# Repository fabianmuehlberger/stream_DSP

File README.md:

## Welcome to GitHub Pages

You can use the [editor on GitHub](https://github.com/fabianmuehlberger/stream_DSP/edit/page/README.md) to maintain and preview the content for your website in Markdown files.

Whenever you commit to this repository, GitHub Pages will run [Jekyll](https://jekyllrb.com/) to rebuild the pages in your site, from the content in your Markdown files.

### Markdown

Markdown is a lightweight and easy-to-use syntax for styling your writing. It includes conventions for

```markdown
Syntax highlighted code block

# Header 1
## Header 2
### Header 3

- Bulleted
- List

1. Numbered
2. List

**Bold** and _Italic_ and `Code` text

[Link](url) and 
```

For more details see [Basic writing and formatting syntax](https://docs.github.com/en/github/writing-on-github/getting-started-with-writing-and-formatting-on-github/basic-writing-and-formatting-syntax).

### Jekyll Themes

Your Pages site will use the layout and styles from the Jekyll theme you have selected in your [repository settings](https://github.com/fabianmuehlberger/stream_DSP/settings/pages). The name of this theme is saved in the Jekyll `_config.yml` configuration file.

### Support or Contact

Having trouble with Pages? Check out our [documentation](https://docs.github.com/categories/github-pages-basics/) or [contact support](https://support.github.com/contact) and we’ll help you sort it out.

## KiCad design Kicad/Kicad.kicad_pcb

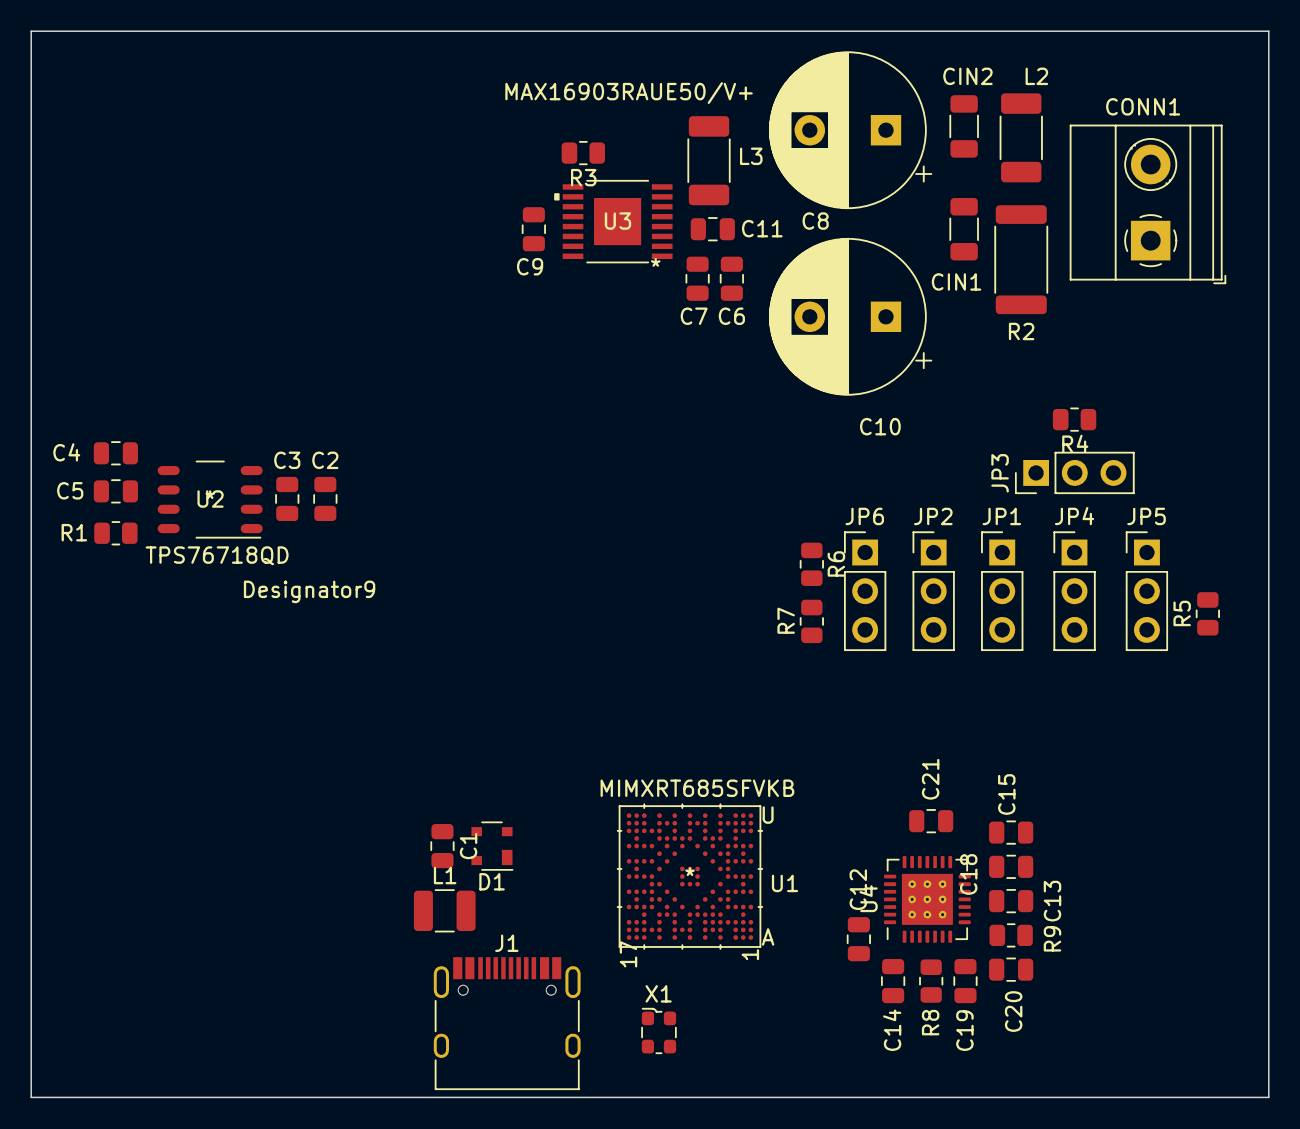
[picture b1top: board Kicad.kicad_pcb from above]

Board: 4 copper layers, 81.2 x 70.0 mm, 47 parts (0 on the bottom side), 38 nets, no tracks yet.

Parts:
C1: 2u2; C_0805_2012Metric
C2, C3, C9, C11, C12, C13, C14, C18, C21: 1u; C_0805_2012Metric
C4, C5: 10uF; C_0805_2012Metric
C6, C7, C15: 4u7; C_0805_2012Metric
C8, C10: 100uF; CP_Radial_D10.0mm_P5.00mm
C19, C20: 2n2; C_0805_2012Metric
CIN1, CIN2: 0.022uF; C_1206_3216Metric
CONN1: Screw_Terminal_01x02; TerminalBlock_Phoenix_MKDS-1,5-2_1x02_P5.00mm_Horizontal
D1: PRTR5V0U2X; SOT-143
J1: USB_C_Receptacle_USB2.0; USB_C_Receptacle_HRO_TYPE-C-31-M-12
JP1, JP2, JP3, JP4, JP5, JP6: Jumper_3_Open; PinHeader_1x03_P2.54mm_Vertical
L1: 330; L_1210_3225Metric
L2: 47; L_2010_5025Metric
L3: 4u7; L_2010_5025Metric
R1: 10k; R_0805_2012Metric
R2: 0.1R; R_2512_6332Metric
R3: 20k; R_0805_2012Metric
R4, R5, R6, R7: 47k; R_0805_2012Metric
R8, R9: 300; R_0805_2012Metric
U1: MIMXRT685SFVKB
U2: TPS76718QD
U3: MAX16903RAUE50/V+; MAX16903RAUE50&slash_V&plus_
U4: ES9033; QFN-28-1EP_5x5mm_P0.5mm_EP3.35x3.35mm_ThermalVias
X1: ECS-2520MV-xxx-xx; Oscillator_SMD_ECS_2520MV-xxx-xx-4Pin_2.5x2.0mm

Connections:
+1V8: U1.A13 (VDD1V8_1), U1.B11 (VDD1V8), U1.C13 (VDD_AO1V8), U1.C16 (VDD1V8), U1.C17 (VDD1V8), U1.D13 (VDD_AO1V8), U1.E4 (VDDA_ADC1V8), U1.E15 (VDD1V8), U1.F13 (VDD1V8), U1.G14 (VDD1V8), U1.L4 (VDD1V8), U1.R15 (VDD1V8)
+3.3V: C12.1, C13.1, C14.1, C21.1, JP1.1 (A), JP2.1 (A), JP3.1 (A), R4.2, R6.2, U4.1 (AVDD), U4.4 (VCCA), U4.9 (AVCC_3V3), U4.17 (AVCC_CP)
+3V3: U1.E6 (VDDIO_1), U1.E8 (VDDIO_1), U1.E10 (VDDIO_1), U1.F5 (VDDIO_0), U1.H5 (VDDIO_0), U1.H13 (VDDIO_1), U1.H14 (VDDIO_1), U1.K5 (VDDIO_0), U1.K13 (VDDIO_1), U1.L14 (VDDIO_1), U1.M5 (VDDIO_0), U1.N6 (VDDIO_0), U1.N8 (VDDIO_0), U1.N10 (VDDIO_0), U1.N12 (VDDIO_2), U1.P11 (VDDIO_2), U1.P12 (VDDIO_2)
/DAC/DAC_OUT1: C19.2, R8.2
/DAC/DAC_OUT2: C20.2, R9.2
/DAC/HW0: JP2.2 (C), U4.22 (MOSI/SDA/HW0)
/DAC/HW1: JP1.2 (C), U4.21 (SCLK/SCL/HW1)
/DAC/HW2: JP4.2 (C), U4.19 (SS/ADDR1/HW2)
/DAC/MODE: JP6.2 (C), U4.3 (MODE)
/DAC/PGND: C15.1, U4.14 (PNEG)
/DSP/XTALIN: U1.B14 (XTALIN), X1.1 (Tri-State)
/DSP/XTALOUT: U1.B13 (XTALOUT), X1.3 (OUT)
/POWER/IN: C2.1, C3.1, U2.3 (IN), U2.4 (IN)
/POWER/VDD_1V8: C4.1, C5.1, R1.2, U2.5 (OUT), U2.6 (OUT)
/POWER/~RESET: R1.1, U2.8 (RESET_N)
/USB/D+: D1.2 (I/O1), J1.A6 (D+), J1.B6 (D+), U1.R17 (USB1_DP)
/USB/D-: D1.3 (I/O2), J1.A7 (D-), J1.B7 (D-), U1.T17 (USB1_DM)
/USB/USB0_VBUS_CON: C1.1, D1.4 (VCC), L1.1
/externl_circuits/5V_BUCK: L3.2, U3.8 (OUTS)
/externl_circuits/BIAS: C9.1, U3.13 (BIAS)
/externl_circuits/BST: C11.1, U3.1 (BST)
/externl_circuits/Buck_LX: C11.2, L3.1, R3.1, U3.4 (LX), U3.5 (LX)
/externl_circuits/PGOOD: R3.2, U3.11 (PGOOD)
/externl_circuits/VSUP: C6.1, C7.1, CONN1.1, R2.1, U3.2 (SUP), U3.3 (SUP)
GND: C1.2, C2.2, C3.2, C4.2, C5.2, C6.2, C7.2, C8.2, C9.2, C10.2, C12.2, C13.2, C14.2, C15.2, C18.2, C19.1, C20.1, C21.2, CIN1.1, CIN2.1, CONN1.2, D1.1 (GND), J1.A1 (GND), J1.A12 (GND), J1.B1 (GND), J1.B12 (GND), J1.S1 (SHIELD), JP1.3 (B), JP2.3 (B), JP5.1 (A), R5.2, R7.2, U1.C3 (VSSA), U1.D5 (VSS), U1.D12 (VSSA), U1.D15 (VSS), U1.E12 (VSS), U1.E14 (VSS), U1.F7 (VSS), U1.F11 (VSS), U1.G6 (VSS), U1.G12 (VSS), U1.H8 (VSS), U1.H9 (VSS), U1.H10 (VSS), U1.J8 (VSS), U1.J10 (VSS), U1.K8 (VSS), U1.K9 (VSS), U1.K10 (VSS), U1.L6 (VSS), U1.L12 (VSS), U1.M7 (VSS), U1.M11 (VSS), U1.M13 (VSS), U1.N14 (VSS), U1.P13 (VSS), U2.1 (GND), U2.2 (EN_N), U3.6 (PGND), U3.7 (PGND), U3.12 (SYNC), U3.14 (GND), U4.5 (DGND), U4.7 (GND_SNS), U4.11 (AGND), U4.13 (AGND_CP), U4.18 (RT1), U4.27 (DGND), U4.29 (PAD), X1.2 (GND)
unnamed: C8.1, C10.1, CIN2.2, L2.2
unnamed: C18.1, U4.12 (BG_VREF)
unnamed: CIN1.2, L2.1, R2.2
unnamed: J1.A4 (VBUS), J1.A9 (VBUS), J1.B4 (VBUS), J1.B9 (VBUS), L1.2
unnamed: JP3.2 (C), JP4.1 (A)
unnamed: JP3.3 (B), R4.1
unnamed: JP4.3 (B), JP5.2 (C)
unnamed: JP5.3 (B), R5.1
unnamed: JP6.1 (A), R6.1
unnamed: JP6.3 (B), R7.1
unnamed: R8.1, U4.6 (OUT1)
unnamed: R9.1, U4.8 (OUT2)
VDDCORE: U1.C5 (VDDCORE), U1.D9 (VDDCORE), U1.F14 (VDDCORE), U1.J4 (VDDCORE), U1.J14 (VDDCORE), U1.P9 (VDDCORE), U1.R5 (VDDCORE), U1.R14 (VDDCORE)

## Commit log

2022-08-11 added NXP dokumentation
    NXP datasheets and application notes
2022-08-14 Set theme jekyll-theme-minimal
2022-08-15 prototyping schematic and PCB
2022-08-16 power section
2022-08-16 Basic Power layout done
2022-08-16 moved Buck to external components sheet
2022-08-26 working on DSP
2022-08-27 changed dac to ES9033
2022-08-27 updated DAC circut
2022-08-28 updated footprints, basic pcb laypout

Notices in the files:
parts and their libraries:
Copyright 2021 Accelerated Designs. All rights reserved.
